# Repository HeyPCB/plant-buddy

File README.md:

# Sprout, the plant buddy

**A circuit-board sprout that cries a little blue tear when your plant is thirsty.**

Sprout is a capacitive soil-moisture stake that lives in a plant pot on one CR2032. Its stem carries a mask-covered electrode; an ATtiny412 times how long that electrode takes to charge through 1 MΩ, and wet soil takes several times longer than dry. When the soil dries out, a blue LED tear drips under its left eye; when the plant is fine it winks. Boop the bud between its gold leaves for an instant answer.

| Layers | Size | Parts | Nets | Connections routed | Vias | ERC errors | DRC errors / unconnected / parity | BOM @100 |
|---|---|---|---|---|---|---|---|---|
| 2 | 40.4 x 128.0 mm | 13 (+3 pads) | 12 | 26 -> 0 open | 22 | 0 | 0 / 0 / 0 | $1.15 |

**Not fabricated, assembled or powered yet.** Every number on this page is measured by KiCad 10.0.6 on
the files in this repository ([`report.json`](report.json), [`measured.json`](measured.json)) or read
from the live JLC/LCSC catalogue ([`bom_cost.json`](bom_cost.json)).

| | |
|---|---|
| Spec, power budget, BOM | [`SPEC.md`](SPEC.md) |
| Store copy | [`STORE_COPY.md`](STORE_COPY.md) |
| KiCad 10 project | [`kicad/`](kicad/) |
| Gerbers, drill, BOM, CPL, STEP, schematic PDF | [`fab/`](fab/) |
| Firmware | [`firmware/`](firmware/) |
| Renders | [front](media/top.png), [back](media/bottom.png), [hero](media/hero.png), [Circuit World thumbnail](media/circuit-world.png) |
| Brief and generator | [`design/`](design/) |

## What's on it

- **Sensor:** a 9 mm-wide electrode down the stem (an F.Cu pour of its own net, under solder mask) over the back's ground plane; no metal touches the soil.
- **MCU:** ATtiny412 (SOIC-8, 1.8-5.5 V), asleep in power-down between 8 s RTC wakes; soil read about once a minute, calibration in EEPROM.
- **Face:** two green 0603 LED eyes, a blue 0603 LED tear, gold blush cheeks, a silk smile; gold leaves with mask-green veins.
- **Button:** the bud (TS-1187A): boop to check, hold 3 s in freshly watered soil to learn wet.
- **Power:** one CR2032 in a Keystone 3034 SMT holder, about two years with a watered plant (SPEC.md).
- **Programming:** three UPDI pads (VCC, UPDI, GND) for any USB-serial adapter.

## Finish

Green solder mask, White silkscreen, ENIG copper finish, 1.6 mm FR4, top-side SMT assembly.
The gold art is bare copper under a mask opening (ENIG), drawn with its own keep-out so no track runs
under it. The QR code on the back opens [https://heypcb.ai/world/b/cdb211161e60](https://heypcb.ai/world/b/cdb211161e60).

## How it was made

Designed with the HeyPCB method on KiCad 10.0.6, headless, by the `heypcb-kicad` pipeline: a written
brief composed from reusable circuit blocks, every pin from KiCad's own symbol library, every part bound
to an LCSC number from a dated catalogue read, then ERC, a netlist round trip, locked placement,
Freerouting 2.4.1, pours, silkscreen and board art, DRC with schematic parity, DFM and a fab gate,
each stage gated by a measurement. `design/make_brief.py` regenerates the brief (outline, part
locks and art) from code.

Part of the [heypcb.ai merch collection](https://github.com/HeyPCB/merch).

## License

Hardware: [CERN-OHL-S v2](LICENSE). Firmware: MIT (see [`firmware/LICENSE`](firmware/LICENSE)). KiCad's symbol, footprint and 3D
libraries used in the design are CC-BY-SA 4.0 with the KiCad library exception.

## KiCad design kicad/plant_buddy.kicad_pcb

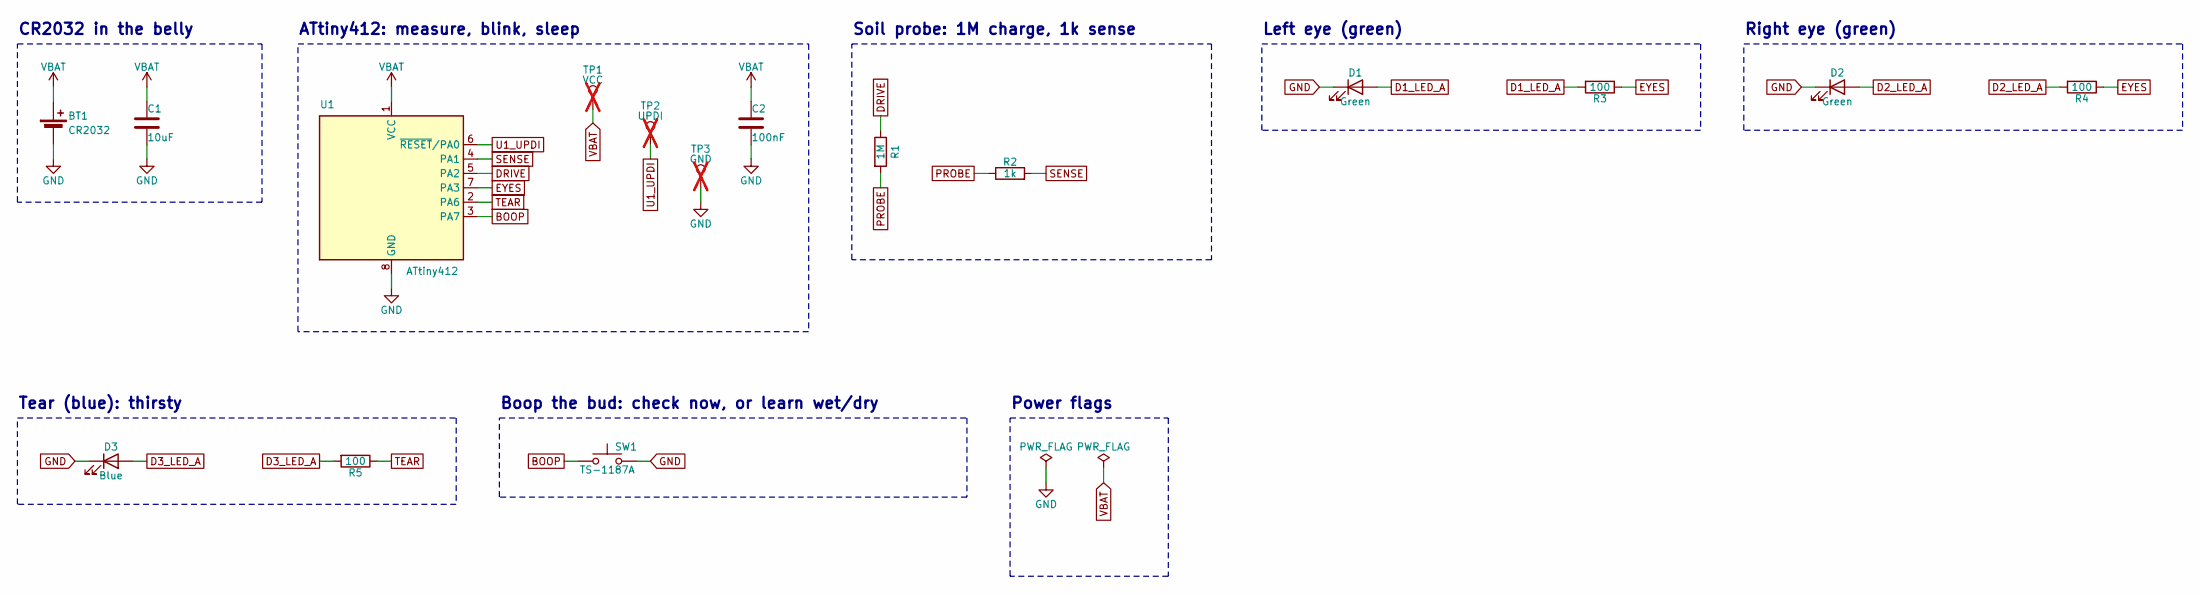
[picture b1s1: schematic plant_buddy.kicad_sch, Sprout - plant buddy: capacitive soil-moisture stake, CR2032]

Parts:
BT1: CR2032; BatteryHolder_Keystone_3034_1x20mm; MPN 3034TR; LCSC C5213768
C1: 10uF; C_0805_2012Metric; MPN CL21A106KAYNNNE; LCSC C15850
C2: 100nF; C_0603_1608Metric; MPN CC0603KRX7R9BB104; LCSC C14663
D1, D2: Green; LED_0603_1608Metric; MPN KT-0603G; LCSC C12624
D3: Blue; LED_0603_1608Metric; MPN NCD0603B1; LCSC C84266
R1: 1M; R_0603_1608Metric; MPN 0603WAF1004T5E; LCSC C22935
R2: 1k; R_0603_1608Metric; MPN 0603WAF1001T5E; LCSC C21190
R3, R4, R5: 100; R_0603_1608Metric; MPN 0603WAF1000T5E; LCSC C22775
SW1: TS-1187A; SW_Push_1P1T_XKB_TS-1187A; MPN TS-1187A-B-A-B; LCSC C318884
TP1: VCC; TestPoint_Pad_1.0x1.0mm; not fitted
TP2: UPDI; TestPoint_Pad_1.0x1.0mm; not fitted
TP3: GND; TestPoint_Pad_1.0x1.0mm; not fitted
U1: ATtiny412; SOIC-8_3.9x4.9mm_P1.27mm; MPN ATTINY412-SSNR; LCSC C1337190

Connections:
BOOP: SW1.1, U1.3 (PA7)
D1_LED_A: D1.2 (A), R3.2
D2_LED_A: D2.2 (A), R4.2
D3_LED_A: D3.2 (A), R5.2
DRIVE: R1.1, U1.5 (PA2)
EYES: R3.1, R4.1, U1.7 (PA3)
GND: BT1.2 (-), C1.2, C2.2, D1.1 (K), D2.1 (K), D3.1 (K), SW1.2, TP3.1, U1.8 (GND)
PROBE: R1.2, R2.1
SENSE: R2.2, U1.4 (PA1)
TEAR: R5.1, U1.2 (PA6)
U1_UPDI: TP2.1, U1.6 (~RESET/PA0)
VBAT: BT1.1 (+), C1.1, C2.1, TP1.1, U1.1 (VCC)

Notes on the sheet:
CR2032 in the belly
ATtiny412: measure, blink, sleep
Soil probe: 1M charge, 1k sense
Left eye (green)
Right eye (green)
Tear (blue): thirsty
Boop the bud: check now, or learn wet/dry
Power flags

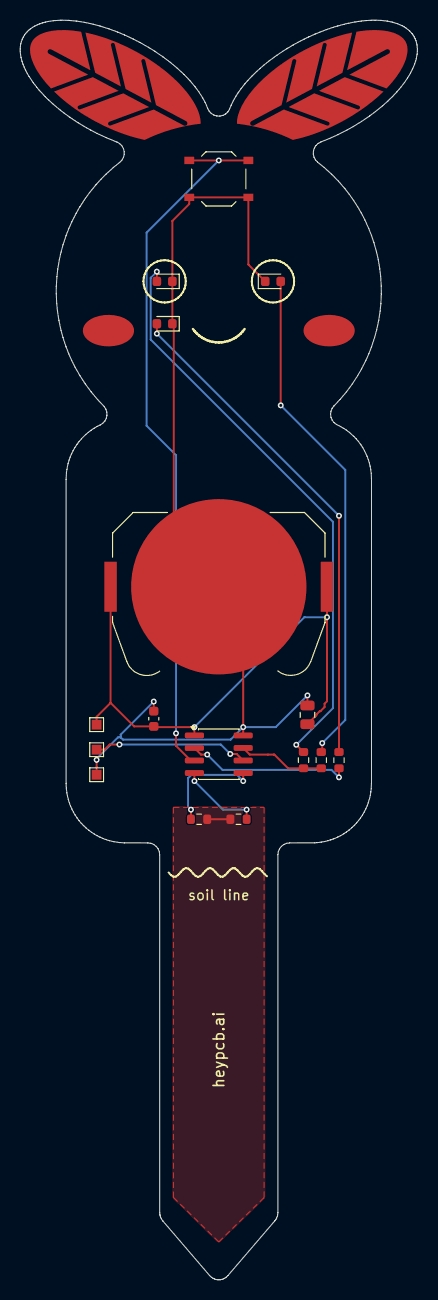
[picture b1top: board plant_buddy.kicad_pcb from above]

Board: 2 copper layers, 40.3 x 127.9 mm, 16 parts (0 on the bottom side), 12 nets.

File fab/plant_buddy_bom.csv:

"Reference","Value","Footprint","MPN","LCSC","Qty"
"BT1","CR2032","Battery:BatteryHolder_Keystone_3034_1x20mm","3034TR","C5213768","1"
"C1","10uF","Capacitor_SMD:C_0805_2012Metric","CL21A106KAYNNNE","C15850","1"
"C2","100nF","Capacitor_SMD:C_0603_1608Metric","CC0603KRX7R9BB104","C14663","1"
"D1,D2","Green","LED_SMD:LED_0603_1608Metric","KT-0603G","C12624","2"
"D3","Blue","LED_SMD:LED_0603_1608Metric","NCD0603B1","C84266","1"
"R1","1M","Resistor_SMD:R_0603_1608Metric","0603WAF1004T5E","C22935","1"
"R2","1k","Resistor_SMD:R_0603_1608Metric","0603WAF1001T5E","C21190","1"
"R3,R4,R5","100","Resistor_SMD:R_0603_1608Metric","0603WAF1000T5E","C22775","3"
"SW1","TS-1187A","Button_Switch_SMD:SW_Push_1P1T_XKB_TS-1187A","TS-1187A-B-A-B","C318884","1"
"U1","ATtiny412","Package_SO:SOIC-8_3.9x4.9mm_P1.27mm","ATTINY412-SSNR","C1337190","1"

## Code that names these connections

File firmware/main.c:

/*
 * Sprout, the plant buddy - firmware for the ATtiny412 (heypcb.ai merch 01).
 *
 * What it does
 *   - Sleeps in power-down; the RTC's periodic interrupt (1 kHz internal oscillator) wakes it every 8 s.
 *   - Every 8th wake (about once a minute) it measures the soil: the stem's mask-covered electrode is
 *     charged through 1M and the MCU counts how long the electrode takes to reach the input's high
 *     threshold. Wetter soil = more capacitance = a longer count. The count is a ratio (RC / threshold),
 *     so it does not move as the coin cell runs down.
 *   - Thirsty: every other wake (16 s) the blue tear "drips" (a soft 120 ms fade). Happy: a double wink
 *     about once a minute.
 *   - Boop the bud (the button): it measures at once and answers (wink = fine, tear + droopy eyes = water me).
 *     Hold it 3 s in freshly watered soil and it learns "wet" (three eye flashes).
 *   - "Air" (the driest possible reading) is learned by itself: it is the lowest count ever seen, kept in
 *     EEPROM. Insert the cell with the stake in open air and that first reading is the baseline.
 *
 * Pins (from the board's netlist; KiCad symbol MCU_Microchip_ATtiny:ATtiny412-SS)
 *   PA1 (pin 4)  SENSE  input, the electrode through 1k
 *   PA2 (pin 5)  DRIVE  output, charges the electrode through 1M
 *   PA3 (pin 7)  EYES   output, both green eye LEDs (high = on, 100 ohm each)
 *   PA6 (pin 2)  TEAR   output, the blue tear LED (high = on, 100 ohm)
 *   PA7 (pin 3)  BOOP   input with pull-up, the button to GND
 *   PA0 (pin 6)  UPDI   programming only
 *
 * Power budget (see SPEC.md for the arithmetic): about 10 uA on average while the plant is happy (about
 * two years on a CR2032), about 17 uA while it cries (well over a year).
 *
 * Build: make      (avr-gcc with ATtiny412 support; see README.md)
 */
#include <avr/eeprom.h>
#include <avr/interrupt.h>
#include <avr/io.h>
#include <avr/sleep.h>
#include <stdint.h>
#include <util/delay.h>

#define SENSE PIN1_bm
#define DRIVE PIN2_bm
#define EYES PIN3_bm
#define TEAR PIN6_bm
#define BOOP PIN7_bm

#define SAMPLES 16            /* charge-time samples averaged per reading */
#define TIMEOUT 60000u        /* counts at 3.33 MHz: 18 ms, far beyond any soil */
#define THIRSTY_PCT 35u       /* thirsty below air + 35 % of the air-to-wet span */
#define HYST_PCT 6u           /* happy again only 6 % of the span above that */
#define HOLD_TO_LEARN_MS 3000u

/* EEPROM: the learned references (0xFFFF = never learned) */
#define EE_AIR ((uint16_t *)0)
#define EE_WET ((uint16_t *)2)

static volatile uint8_t boop_flag;
static uint16_t air, wet;
static uint8_t thirsty;

ISR(RTC_PIT_vect) { RTC.PITINTFLAGS = RTC_PI_bm; }

ISR(PORTA_PORT_vect)
{
    PORTA.INTFLAGS = BOOP;          /* PA7 is not fully asynchronous: BOTHEDGES is what wakes power-down */
    boop_flag = 1;
}

/* One charge time, in CPU clocks (3.33 MHz): discharge the electrode, then time it through 1M. */
static uint16_t charge_counts(void)
{
    PORTA.OUTCLR = DRIVE | SENSE;
    PORTA.DIRSET = DRIVE | SENSE;   /* both low: empty the electrode through the 1k */
    _delay_us(300);
    PORTA.DIRCLR = SENSE;           /* sense becomes a high-impedance input */
    cli();
    TCA0.SINGLE.CNT = 0;
    PORTA.OUTSET = DRIVE;           /* start charging */
    while (!(PORTA.IN & SENSE) && TCA0.SINGLE.CNT < TIMEOUT)
        ;
    uint16_t n = TCA0.SINGLE.CNT;
    sei();
    PORTA.OUTCLR = DRIVE;           /* leave it at 0 V: no floating input while asleep */
    return n;
}

static uint16_t measure(void)
{
    uint32_t sum = 0;
    TCA0.SINGLE.CTRLA = TCA_SINGLE_CLKSEL_DIV1_gc | TCA_SINGLE_ENABLE_bm;
    for (uint8_t i = 0; i < SAMPLES; i++)
        sum += charge_counts();
    TCA0.SINGLE.CTRLA = 0;          /* timer off again */
    return (uint16_t)(sum / SAMPLES);
}

static uint16_t span(void) { return (wet > air) ? (uint16_t)(wet - air) : 1u; }

/* Update the thirsty flag from one reading, with hysteresis; track the driest reading as "air". */
static void judge(uint16_t r)
{
    if (r < air) {
        air = r;
        eeprom_update_word(EE_AIR, air);    /* only ever goes down: a handful of writes in its life */
    }
    uint16_t low = air + (uint16_t)(((uint32_t)span() * THIRSTY_PCT) / 100u);
    uint16_t high = low + (uint16_t)(((uint32_t)span() * HYST_PCT) / 100u);
    if (r < low)
        thirsty = 1;
    else if (r > high)
        thirsty = 0;
}

/* ---- little LED animations (software PWM at about 1 kHz, a few mA for a few ms) ---- */
static void glow(uint8_t pin, uint8_t from, uint8_t to, uint8_t steps_ms)
{
    for (uint8_t t = 0; t < steps_ms; t++) {
        uint8_t level = from + (int16_t)(to - from) * t / steps_ms;     /* 0..32 */
        for (uint8_t k = 0; k < 32; k++) {
            if (k < level)
                PORTA.OUTSET = pin;
            else
                PORTA.OUTCLR = pin;
            _delay_us(30);
        }
    }
    PORTA.OUTCLR = pin;
}

static void tear_drip(void) { glow(TEAR, 0, 32, 40); glow(TEAR, 32, 0, 80); }

static void wink(void)
{
    PORTA.OUTSET = EYES; _delay_ms(30); PORTA.OUTCLR = EYES; _delay_ms(140);
    PORTA.OUTSET = EYES; _delay_ms(30); PORTA.OUTCLR = EYES;
}

static void droop(void) { glow(EYES, 20, 0, 250); }

static void learned(void)
{
    for (uint8_t i = 0; i < 3; i++) {
        PORTA.OUTSET = EYES; _delay_ms(70); PORTA.OUTCLR = EYES; _delay_ms(110);
    }
}

static void answer(void)
{
    if (thirsty) {
        PORTA.OUTSET = TEAR;
        droop();
        PORTA.OUTCLR = TEAR;
    } else {
        wink();
    }
}

static void on_boop(void)
{
    _delay_ms(25);                          /* debounce */
    if (PORTA.IN & BOOP)
        return;                             /* a release edge, or a bounce */
    uint16_t r = measure();
    judge(r);
    answer();
    uint16_t held = 0;
    while (!(PORTA.IN & BOOP) && held < HOLD_TO_LEARN_MS) {
        _delay_ms(10);
        held += 10;
    }
    if (held >= HOLD_TO_LEARN_MS) {
        wet = measure();                    /* freshly watered soil: the "wet" reference */
        if (wet <= air + 4)
            wet = air + 4;                  /* never a zero span */
        eeprom_update_word(EE_WET, wet);
        thirsty = 0;
        learned();
        while (!(PORTA.IN & BOOP))
            ;                               /* wait for the release */
    }
}

static void sleep_now(void)
{
    set_sleep_mode(SLEEP_MODE_PWR_DOWN);
    sleep_enable();
    sleep_cpu();
    sleep_disable();
}

int main(void)
{
    /* outputs low, the button's pull-up and wake-up edge */
    PORTA.DIRSET = DRIVE | EYES | TEAR;
    PORTA.OUTCLR = DRIVE | EYES | TEAR;
    PORTA.PIN7CTRL = PORT_PULLUPEN_bm | PORT_ISC_BOTHEDGES_gc;

    /* RTC periodic interrupt: 1.024 kHz internal ULP, 8192 cycles = 8 s */
    while (RTC.STATUS > 0)
        ;
    RTC.CLKSEL = RTC_CLKSEL_INT1K_gc;
    while (RTC.PITSTATUS > 0)
        ;
    RTC.PITINTCTRL = RTC_PI_bm;
    RTC.PITCTRLA = RTC_PERIOD_CYC8192_gc | RTC_PITEN_bm;
    sei();

    /* references: air is the first reading after a fresh flash, wet a guess until it is taught */
    uint16_t first = measure();
    air = eeprom_read_word(EE_AIR);
    wet = eeprom_read_word(EE_WET);
    if (air == 0xFFFF || first < air) {
        air = first;
        eeprom_update_word(EE_AIR, air);
    }
    if (wet == 0xFFFF || wet <= air)
        wet = air * 3u;                     /* untaught: soil at three times the air capacitance */
    judge(first);
    wink();                                 /* hello */

    uint8_t tick = 0;
    for (;;) {
        sleep_now();
        if (boop_flag) {
            boop_flag = 0;
            on_boop();
            continue;
        }
        if ((++tick & 7u) == 0)             /* about once a minute */
            judge(measure());
        if (thirsty) {
            if (tick & 1u)                  /* a tear every 16 s: about 15 uA, see SPEC.md */
                tear_drip();
        } else if ((tick & 7u) == 4u) {
            wink();                         /* happy: a double wink about once a minute */
        }
    }
}
